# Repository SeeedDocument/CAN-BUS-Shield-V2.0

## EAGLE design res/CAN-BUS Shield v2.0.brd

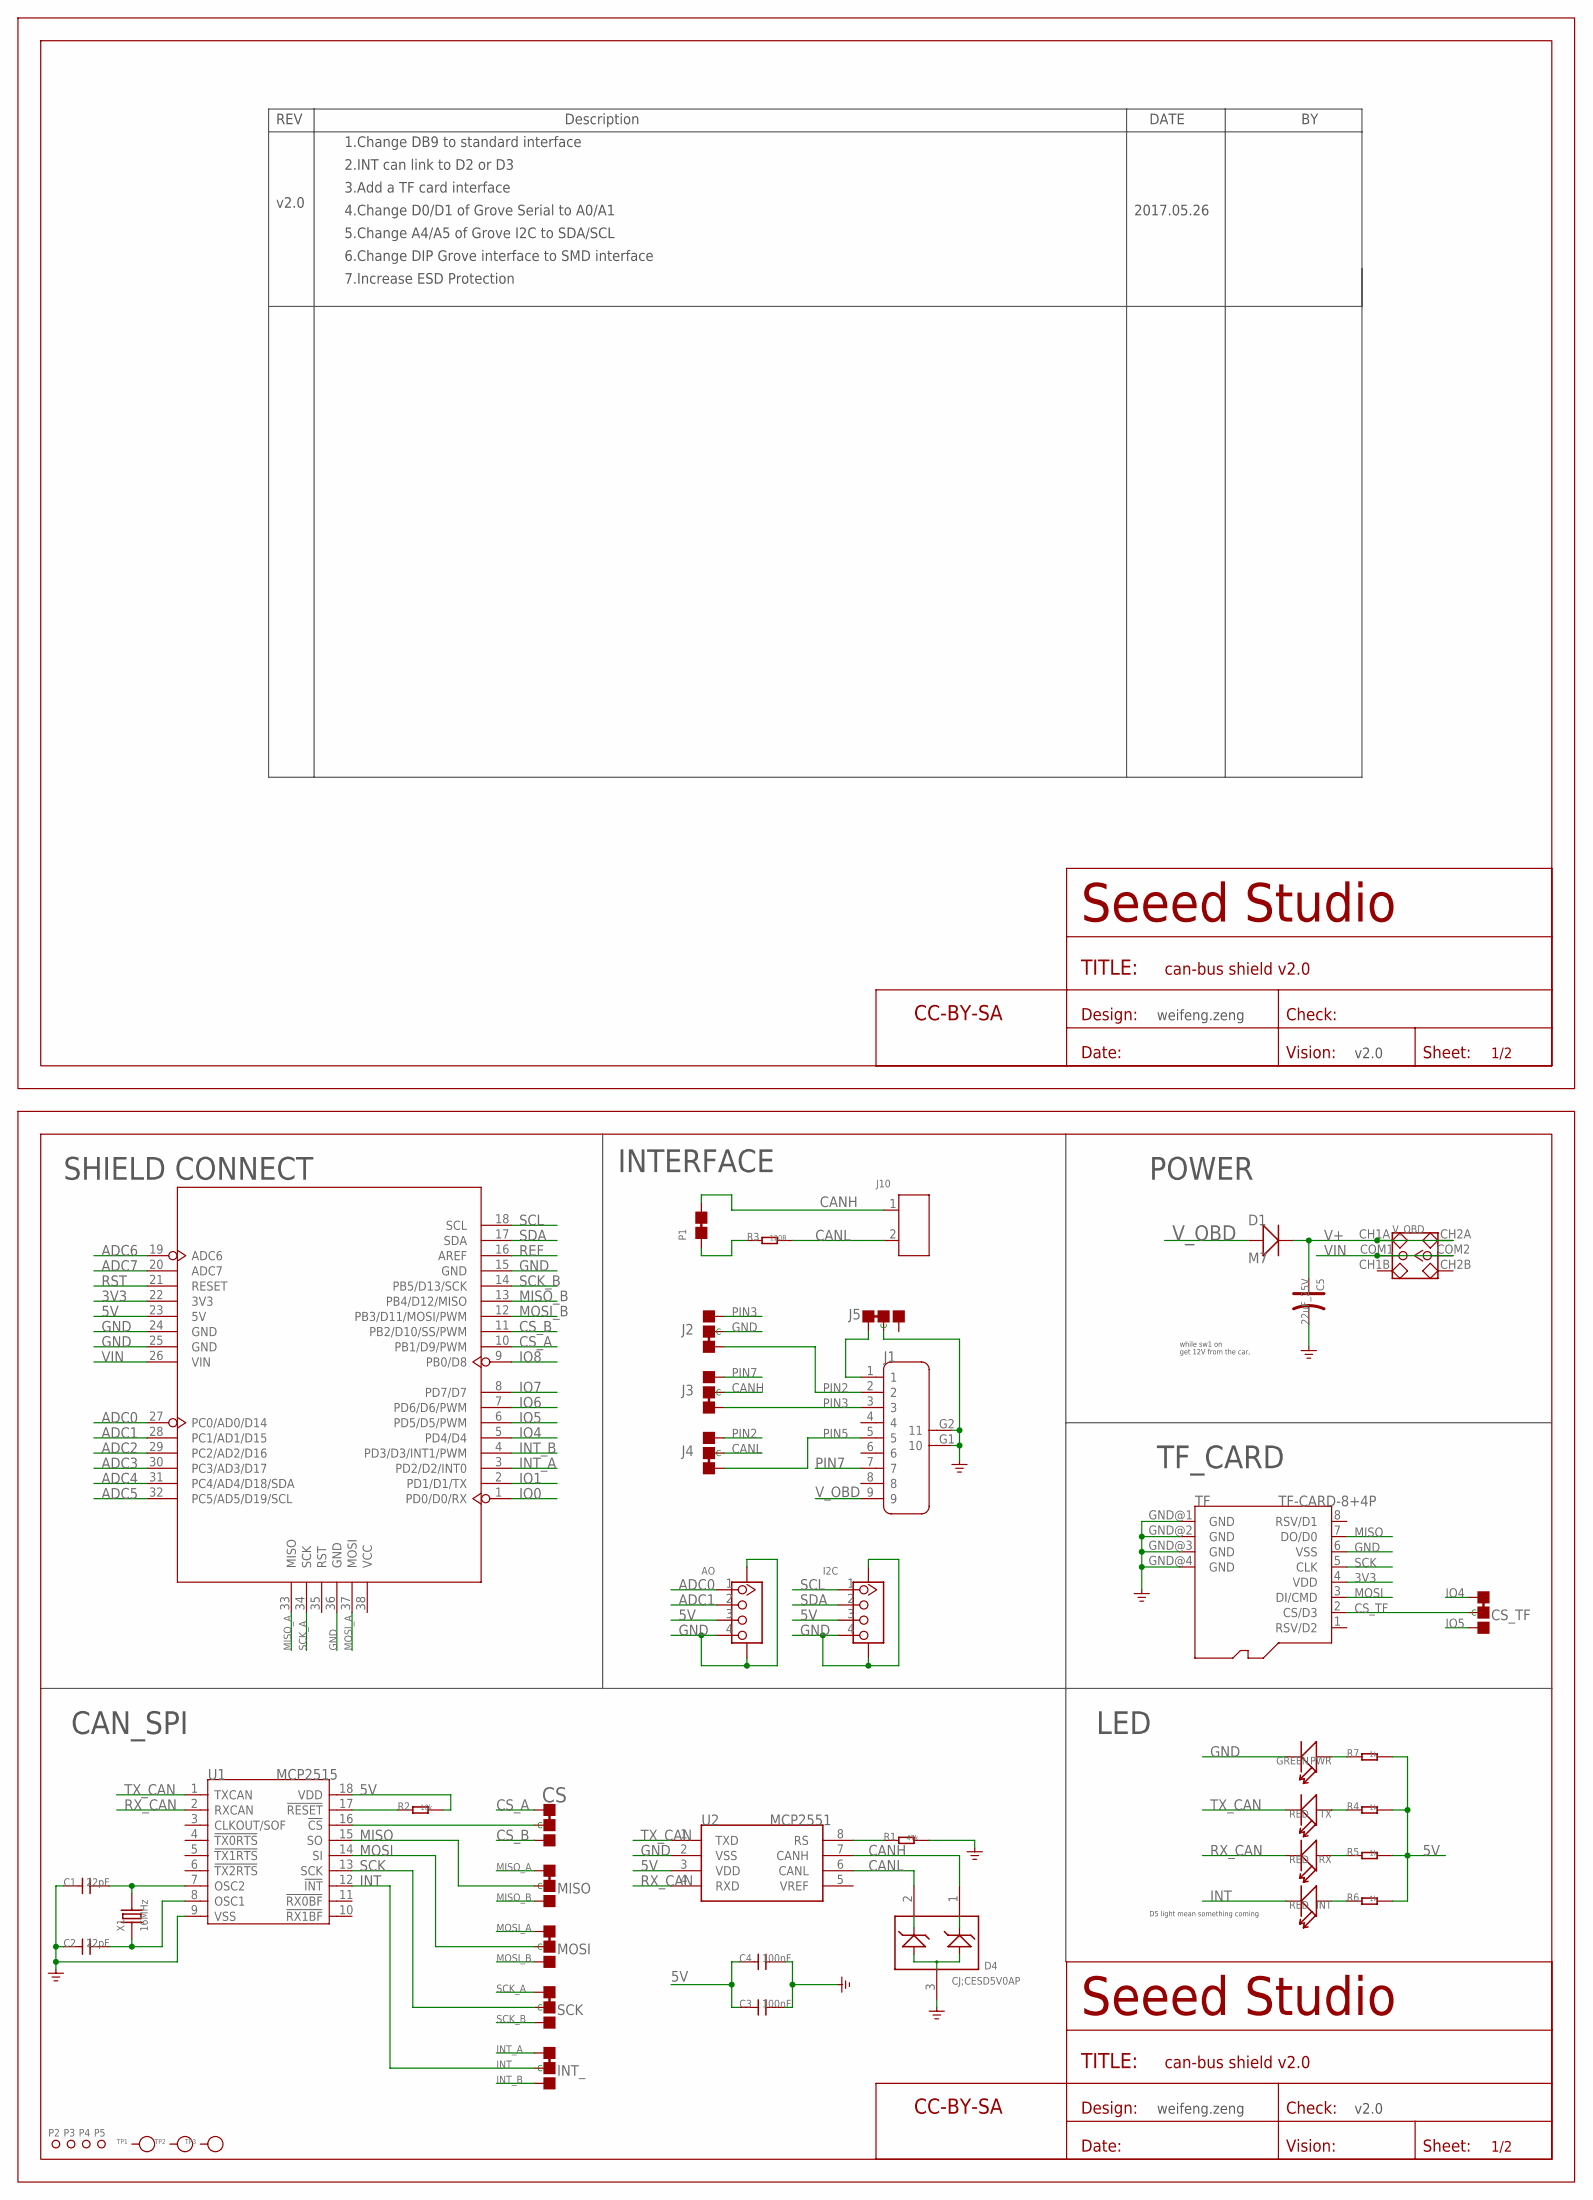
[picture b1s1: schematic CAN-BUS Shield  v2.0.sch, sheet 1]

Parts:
AO: GROVE-CONNECTOR-SMD'90D'; HW4-SMD-2.0-90D
C1, C2: 22pF; 0603
C3, C4: 100nF; 0603
C5: 22uF_25V; ELECTRO-SMD-B-4.8MM
CS: JUMPER-3P-SHORT; 3P-SMD-SHORT
CS_TF: JUMPER-3P-SHORT; 3P-SMD-SHORT
D1: M7; D2010
D4: CJ;CESD5V0AP; SOT-23
I2C: GROVE-CONNECTOR-SMD'90D'; HW4-SMD-2.0-90D
INT: RED; LED-0603
INT_: JUMPER-3P-SHORT; 3P-SMD-SHORT
J1: DB9'MEAL'; DB9-MEAL
J2, J3, J4, J5: JUMPER-3P-SHORT; 3P-SMD-SHORT
J10: SCREW-TERMINAL-2P-10.6X10; H2-5.0-10.6X10X14.8H
MISO: JUMPER-3P-SHORT; 3P-SMD-SHORT
MOSI: JUMPER-3P-SHORT; 3P-SMD-SHORT
P1: JUMPER-2P-SHORT; 2P-SMD-SHORT
P2, P3, P4, P5: PAD-MARK'ANNULAR'; ROUND-MARK-1.0
PWR: GREEN; LED-0603
R1: 47k; 0603
R2: 10k; 0603
R3: 120R; 0603
R4, R5, R6, R7: 1k; 0603
RX: RED; LED-0603
SCK: JUMPER-3P-SHORT; 3P-SMD-SHORT
TF: TF-CARD-8+4P; TF-8+4P-1.1-13.5X15MM
TP1, TP2, TP3: PAD-TEST-POINT'4545'; TP_4545
TX: RED; LED-0603
U1: MCP2515; SOIC18
U2: MCP2551; SOIC8-6.0
U4: ARDUINO-38P'WITH/-SILK'; ARDUINO-38P-WITH/-SILK-500519002
U$5, U$7: SEEEDSTUDIO-OPEN-SCH-FRAME; SEEEDSTUDIO-PCB-FRAME
V_OBD: SWITCH-2CH-6P; 6P-2CH-2.54-7.6X3.0
X1: 16MHz; HC49/S

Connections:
3V3: TF.4 (VDD), U4.22 (3V3)
5V: AO.3, C3.1, C4.1, I2C.3, R2.2, R4.2, R5.2, R6.2, R7.2, U1.18 (VDD), U2.3 (VDD), U4.23 (5V)
ADC0: AO.1, U4.27 (PC0/AD0/D14)
ADC1: AO.2, U4.28 (PC1/AD1/D15)
ADC2: U4.29 (PC2/AD2/D16)
ADC3: U4.30 (PC3/AD3/D17)
ADC4: U4.31 (PC4/AD4/D18/SDA)
ADC5: U4.32 (PC5/AD5/D19/SCL)
ADC6: U4.19 (ADC6)
ADC7: U4.20 (ADC7)
CANH: D4.1, J3.MM (C), J10.1, P1.2, U2.7 (CANH)
CANL: D4.2, J4.MM (C), J10.2, R3.2, U2.6 (CANL)
CS_A: CS.11 (L), U4.10 (PB1/D9/PWM)
CS_B: CS.00 (R), U4.11 (PB2/D10/SS/PWM)
CS_TF: CS_TF.MM (C), TF.2 (CS/D3)
GND: AO.4, AO.SS1, AO.SS2, C1.1, C2.1, C3.2, C4.2, C5.-, D4.3, I2C.4, I2C.SS1, I2C.SS2, J1.G1 (10), J1.G2 (11), J2.MM (C), J5.MM (C), PWR.-, R1.2, TF.6 (VSS), TF.GND@1 (GND), TF.GND@2 (GND), TF.GND@3 (GND), TF.GND@4 (GND), U1.9 (VSS), U2.2 (VSS), U4.15 (GND), U4.24 (GND), U4.25 (GND), U4.36 (GND)
INT: INT.-, INT_.MM (C), U1.12 (!INT)
INT_A: INT_.11 (L), U4.3 (PD2/D2/INT0)
INT_B: INT_.00 (R), U4.4 (PD3/D3/INT1/PWM)
IO0: U4.1 (PD0/D0/RX)
IO1: U4.2 (PD1/D1/TX)
IO4: CS_TF.11 (L), U4.5 (PD4/D4)
IO5: CS_TF.00 (R), U4.6 (PD5/D5/PWM)
IO6: U4.7 (PD6/D6/PWM)
IO7: U4.8 (PD7/D7)
IO8: U4.9 (PB0/D8)
MISO: MISO.MM (C), TF.7 (DO/D0), U1.15 (SO)
MISO_A: MISO.11 (L), U4.33 (MISO)
MISO_B: MISO.00 (R), U4.13 (PB4/D12/MISO)
MOSI: MOSI.MM (C), TF.3 (DI/CMD), U1.14 (SI)
MOSI_A: MOSI.11 (L), U4.37 (MOSI)
MOSI_B: MOSI.00 (R), U4.12 (PB3/D11/MOSI/PWM)
unnamed: PWR.+, R7.1
unnamed: R4.1, TX.+
unnamed: P1.1, R3.1
unnamed: J1.1, J5.11 (L)
unnamed: CS.MM (C), U1.16 (!CS)
unnamed: R5.1, RX.+
unnamed: C1.2, U1.7 (OSC2), X1.2
unnamed: C2.2, U1.8 (OSC1), X1.1
unnamed: INT.+, R6.1
unnamed: R1.1, U2.8 (RS)
PIN2: J1.2, J2.11 (L), J4.00 (R)
PIN3: J1.3, J2.00 (R), J3.11 (L)
PIN5: J1.5, J4.11 (L)
PIN7: J1.7, J3.00 (R)
REF: U4.16 (AREF)
RST: U4.21 (RESET)
RST_N: R2.1, U1.17 (!RESET)
RX_CAN: RX.-, U1.2 (RXCAN), U2.4 (RXD)
SCK: SCK.MM (C), TF.5 (CLK), U1.13 (SCK)
SCK_A: SCK.11 (L), U4.34 (SCK)
SCK_B: SCK.00 (R), U4.14 (PB5/D13/SCK)
SCL: I2C.1, U4.18 (SCL)
SDA: I2C.2, U4.17 (SDA)
TX_CAN: TX.-, U1.1 (TXCAN), U2.1 (TXD)
V+: C5.+, D1.-, V_OBD.CH1A, V_OBD.CH2A
VIN: U4.26 (VIN), V_OBD.COM1, V_OBD.COM2
V_OBD: D1.+, J1.9

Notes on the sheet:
CAN_SPI
SHIELD CONNECT
INTERFACE
POWER
get 12V from the car,
D5 light mean something coming
while sw1 on
TF_CARD
LED
v2.0
1.Change DB9 to standard interface
2.INT can link to D2 or D3
3.Add a TF card interface
4.Change D0/D1 of Grove Serial to A0/A1
5.Change A4/A5 of Grove I2C to SDA/SCL
6.Change DIP Grove interface to SMD interface
2017.05.26
7.Increase ESD Protection
weifeng.zeng

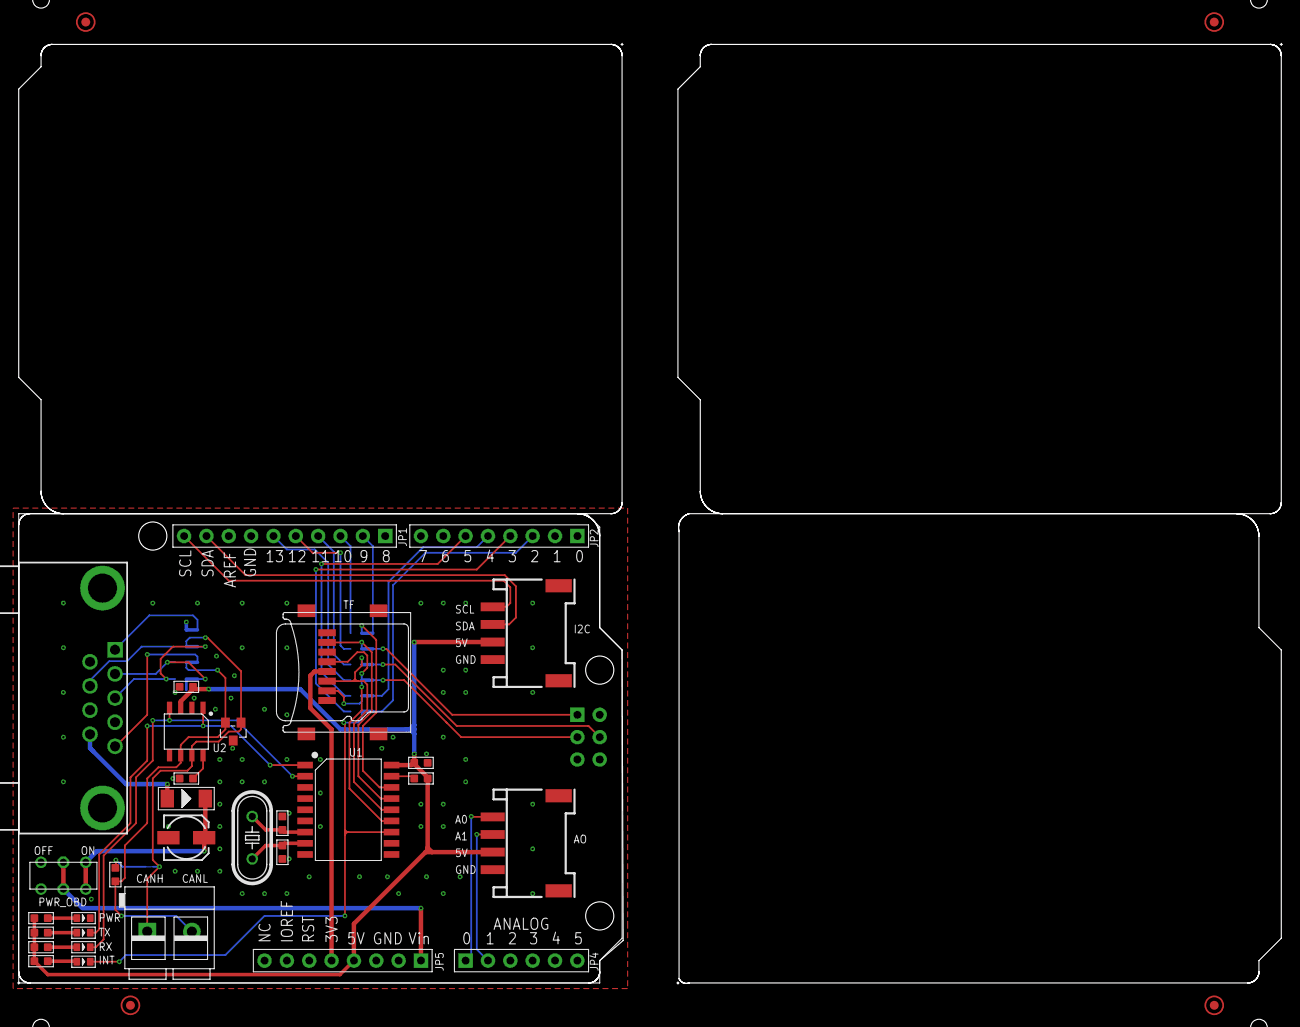
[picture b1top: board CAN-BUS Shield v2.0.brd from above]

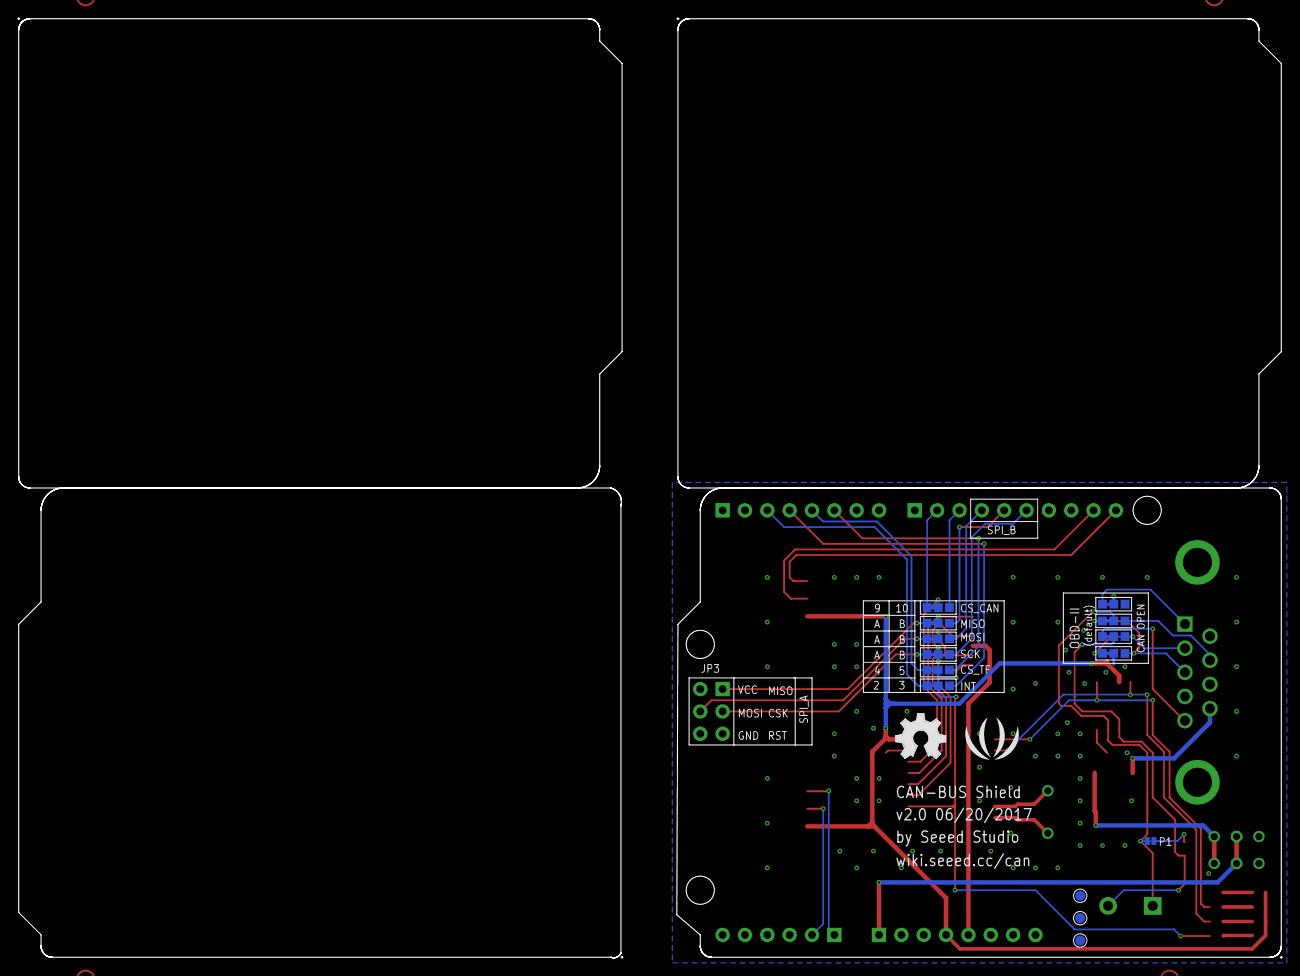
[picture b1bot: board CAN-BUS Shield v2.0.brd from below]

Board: 2 copper layers, 143.7 x 106.9 mm, 50 parts (16 on the bottom side), 46 nets.

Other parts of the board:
U$1: LOGO_SILK
U$2: GND_POWER; OSHW_FILLX200_NOTEXT

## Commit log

2017-08-15 upup
2019-05-07 add the drawings
2019-05-07 add the drawing
2019-11-05 add
    add

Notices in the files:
parts and their libraries:
moudle-new: This work is licensed under the Creative Commons Attribution 4.0 International License.
To view a copy of this license,visit:
http://creativecommons.org/licenses/by-sa/4.0
moudle-new: CC-BY-SA
